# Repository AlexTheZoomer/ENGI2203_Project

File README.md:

# 🏛️ Integrated Security System for Museum & Showcase Environments 

## Project Overview
This project is an **Integrated Security System** designed for museum and showcase environments, providing security through **object tagging, proximity detection, and real-time monitoring**. The following repository will be holding the software project components (C Files & Solidworks Models). Future iterations may include automated alerts. The system aims to mitigate **theft, unauthorized access, and display damage**, while also offering valuable data for monitoring and management.

## Features
- **RFID-Based Pedestal Monitoring**
- **Tiered Alert System** with LED Indicators & Alarms
- **Automated Security Responses** (Door Closures, Logs, Alarms)
- **Low-Cost Implementation** using **Arduino Nano Compatible Boards**
- **Integration with Museum Databases** for authentication

## Functional Requirements
### 1. Pedestal Authorization System
- A **photoresistor** detects object presence.
- The object **communicates via RFID** with the pedestal.
- If the RFID tag matches the database, a **green LED** confirms correct placement.
- If removed or mismatched, **warning and alarm sequences** initiate.

### 2. Security Events
Each event corresponds with a different LED and response:
| Event | LED Color | Response |
|---|---|---|
| Correct Placement | Green | Normal Operation |
| Missing Item | Orange | Slow Beep & Warning |
| Incorrect Item | Blue | Long Alarm Beep |
| Unauthorized Item | Red | Fast Alarm, Door Lock |

### 3. Automated Door System
- Remains open with correct placement.
- Closes after item removal if **security escalation** occurs.

## Hardware Components
- **Microcontroller:** ATMega328p (Arduino Nano compatible)
- **RFID Receiver & Transmitter Modules**
- **Photoresistors for Object Detection**
- **LED Indicators** (Green, Orange, Blue, Red)
- **Alarm Speaker**
- **Servo Motor for Door Automation**

## Software Components
- **Embedded C Code** to manage:
  - Authentication
  - Security Protocols
  - Logging System Events
- **Logging & Audit Trail** for museum security personnel

## Installation & Setup
1. Mount **pedestal module** and connect power.
2. Attach RFID tags to **displayed artifacts**.
3. Load **museum database IDs** onto the system.
4. Configure security thresholds and responses.

## Team Members & Roles
- **Alexandre DesAulniers** - Communications Lead & GitHub Management
- **Mason Allain** - Hardware Design Lead
- **Michael Gallant** - Software Design Lead
- **Sadie Fowlow** - Team Member

## Project Timeline
| Milestone | Date |
|---|---|
| Conceptual Design & Planning | February 12, 2025 |
| Hardware Prototyping Begins | March 1, 2025 |
| Functional Prototype Completed | March 17, 2025 |
| Final Testing & Report | April 7, 2025 |

## Future Work
- **Enhance RFID Security Measures** (Encryption & Anti-Tamper Features)
- **Improve False Alarm Mitigation**
- **Develop Remote Monitoring Dashboard**
- **Expand Compatibility with Existing Museum Security Systems**

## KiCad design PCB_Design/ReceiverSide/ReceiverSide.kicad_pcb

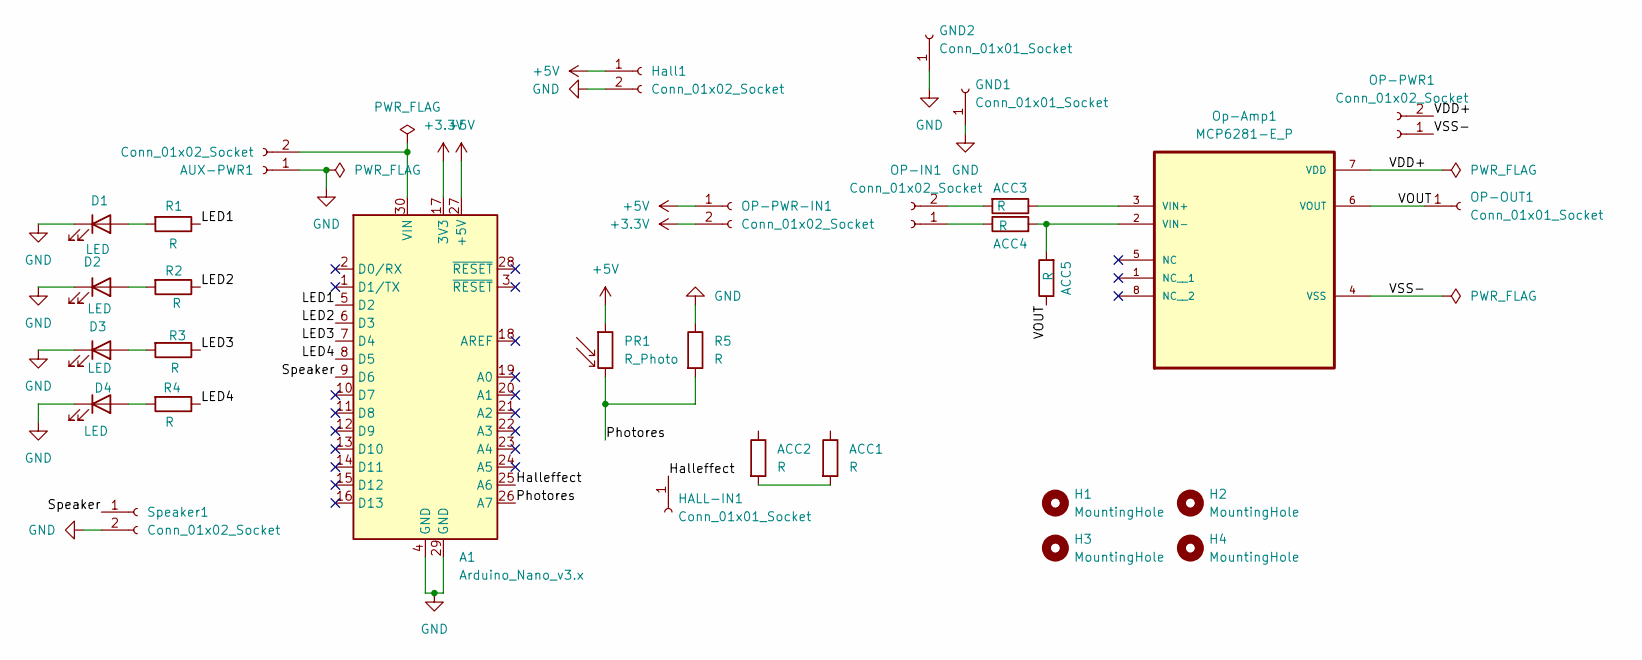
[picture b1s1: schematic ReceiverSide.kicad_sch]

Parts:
A1: Arduino_Nano_v3.x; Arduino_Nano
ACC1, ACC2, ACC3, ACC4, ACC5: R; R_Axial_DIN0204_L3.6mm_D1.6mm_P5.08mm_Horizontal
AUX-PWR1: Conn_01x02_Socket; PinSocket_1x02_P2.54mm_Vertical
D1, D2, D3, D4: LED; LED_D3.0mm
GND1, GND2: Conn_01x01_Socket; PinSocket_1x01_P2.54mm_Vertical
H1, H2, H3, H4: MountingHole; MountingHole_2.7mm
HALL-IN1: Conn_01x01_Socket; PinSocket_1x01_P2.54mm_Vertical
Hall1: Conn_01x02_Socket; PinSocket_1x02_P2.54mm_Vertical
OP-IN1: Conn_01x02_Socket; PinSocket_1x02_P2.54mm_Vertical
OP-OUT1: Conn_01x01_Socket; PinSocket_1x01_P2.54mm_Vertical
OP-PWR1: Conn_01x02_Socket; PinSocket_1x02_P2.54mm_Vertical
OP-PWR-IN1: Conn_01x02_Socket; PinSocket_1x02_P2.54mm_Vertical
Op-Amp1: MCP6281-E_P; DIP787W46P254L927H533Q8
PR1: R_Photo; R_Axial_DIN0204_L3.6mm_D1.6mm_P5.08mm_Horizontal
R1, R2, R3, R4, R5: R; R_Axial_DIN0204_L3.6mm_D1.6mm_P5.08mm_Horizontal
Speaker1: Conn_01x02_Socket; PinSocket_1x02_P2.54mm_Vertical

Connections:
+3.3V: A1.17 (3V3), OP-PWR-IN1.2
+5V: A1.27 (+5V), Hall1.1, OP-PWR-IN1.1, PR1.1
/Halleffect: A1.25 (A6), HALL-IN1.1
/LED1: A1.5 (D2), R1.1
/LED2: A1.6 (D3), R2.1
/LED3: A1.7 (D4), R3.1
/LED4: A1.8 (D5), R4.1
/Photores: A1.26 (A7), PR1.2, R5.2
/Speaker: A1.9 (D6), Speaker1.1
/VDD+: OP-PWR1.2, Op-Amp1.7 (VDD)
/VOUT: ACC5.1, OP-OUT1.1, Op-Amp1.6 (VOUT)
/VSS-: OP-PWR1.1, Op-Amp1.4 (VSS)
GND: A1.4 (GND), A1.29 (GND), AUX-PWR1.1, D1.1 (K), D2.1 (K), D3.1 (K), D4.1 (K), GND1.1, GND2.1, Hall1.2, R5.1, Speaker1.2
unnamed: A1.30 (VIN), AUX-PWR1.2
unnamed: ACC1.2, ACC2.2
unnamed: D1.2 (A), R1.2
unnamed: D2.2 (A), R2.2
unnamed: D3.2 (A), R3.2
unnamed: D4.2 (A), R4.2
unnamed: ACC4.1, OP-IN1.1
unnamed: ACC3.2, OP-IN1.2
unnamed: ACC3.1, Op-Amp1.3 (VIN+)
unnamed: ACC4.2, ACC5.2, Op-Amp1.2 (VIN-)

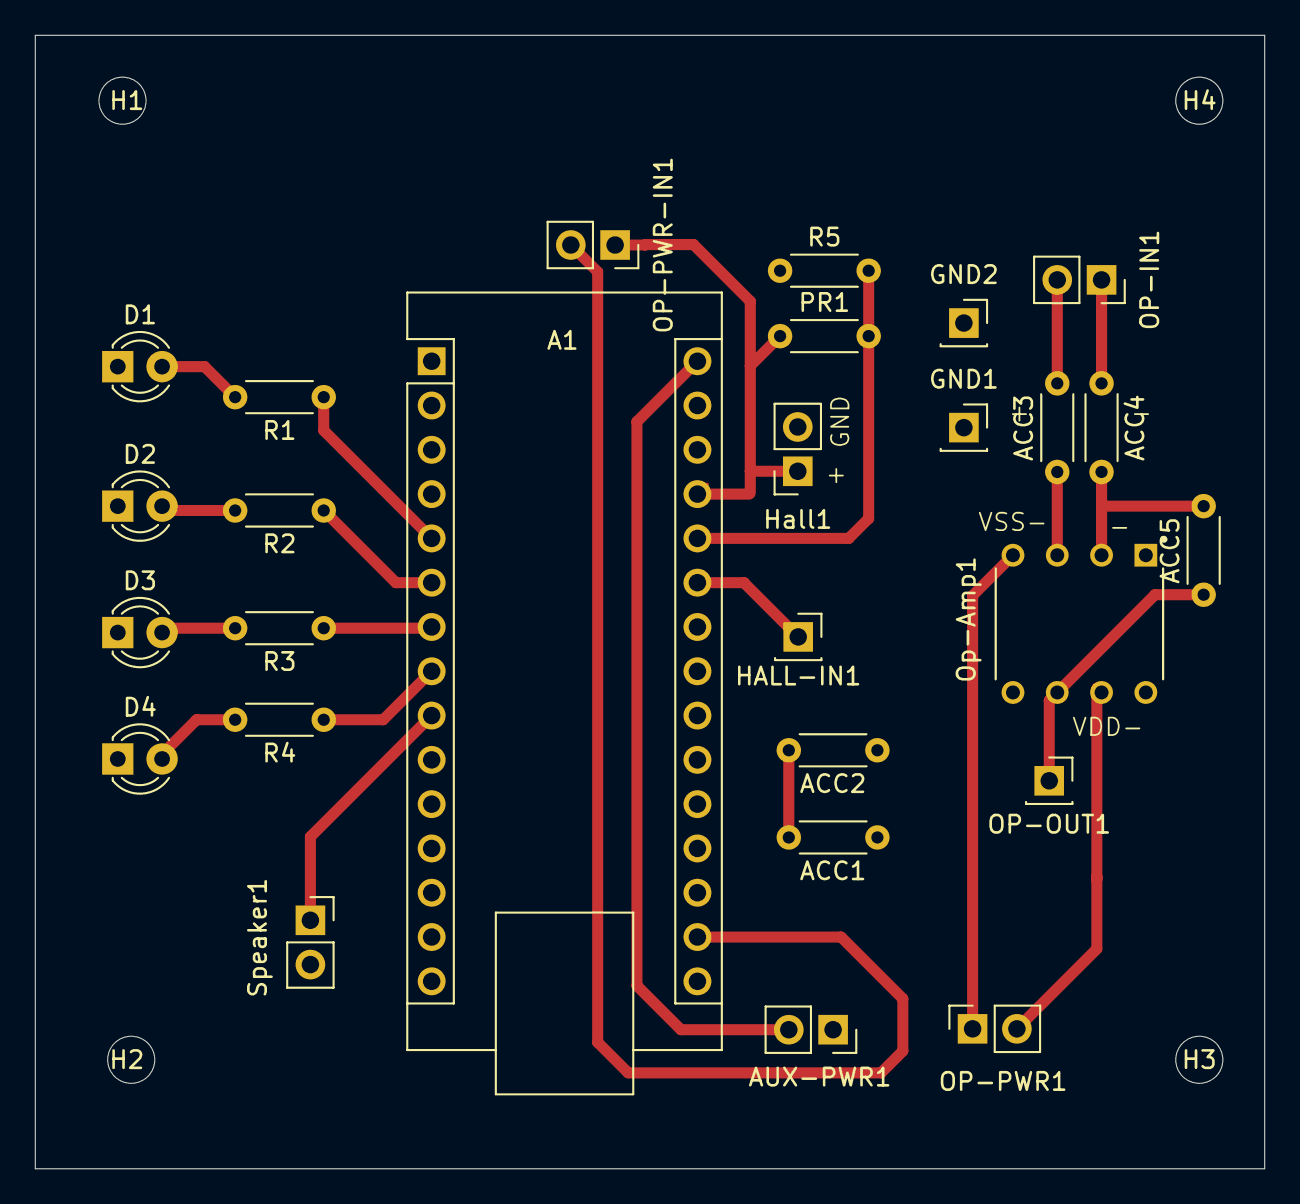
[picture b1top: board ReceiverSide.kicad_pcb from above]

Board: 2 copper layers, 70.5 x 65.0 mm, 31 parts (0 on the bottom side), 23 nets.

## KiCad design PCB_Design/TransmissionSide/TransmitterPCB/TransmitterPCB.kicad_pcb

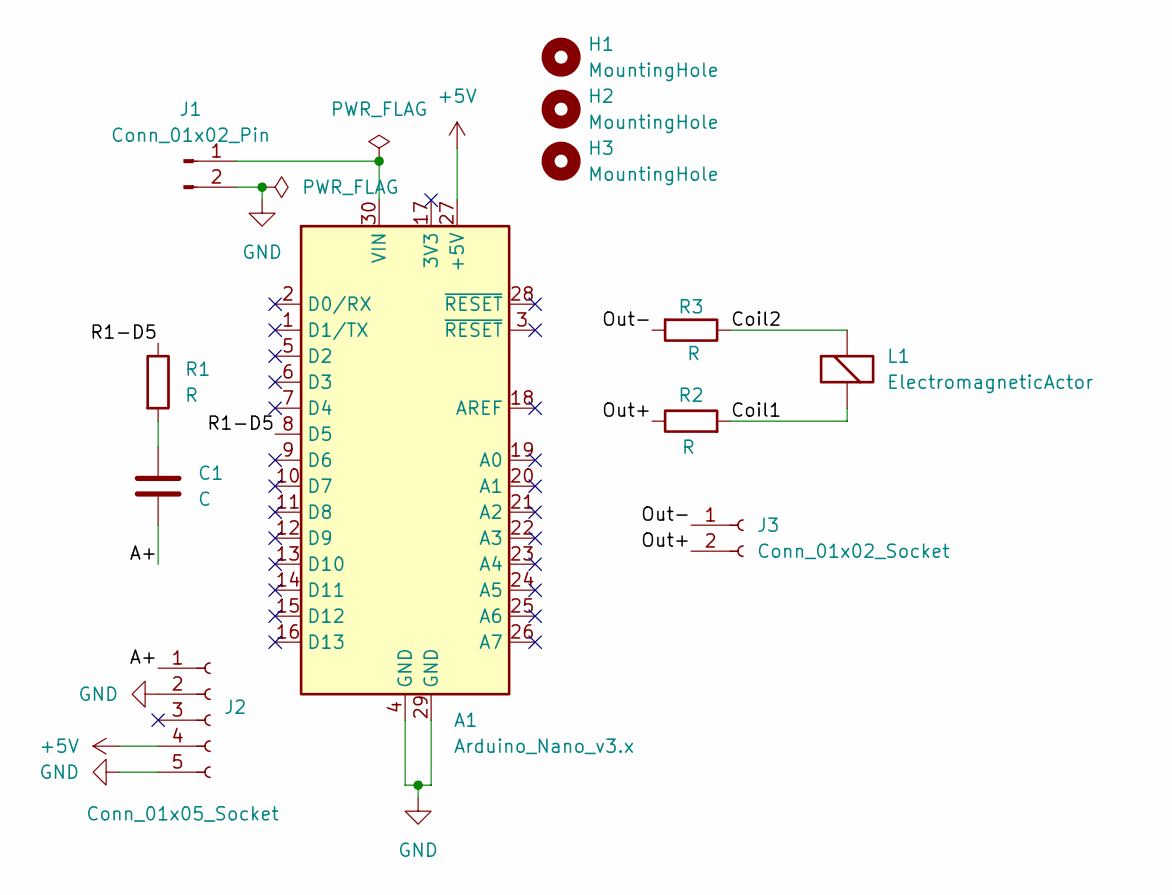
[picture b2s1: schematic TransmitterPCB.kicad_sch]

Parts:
A1: Arduino_Nano_v3.x; Arduino_Nano
C1: C; R_Axial_DIN0204_L3.6mm_D1.6mm_P5.08mm_Horizontal
H1, H2, H3: MountingHole; MountingHole_2.7mm
J1: Conn_01x02_Pin; PinSocket_1x02_P2.54mm_Vertical
J2: Conn_01x05_Socket; PinSocket_1x05_P2.54mm_Vertical
J3: Conn_01x02_Socket; R_Axial_DIN0204_L3.6mm_D1.6mm_P5.08mm_Horizontal
L1: ElectromagneticActor; R_Axial_DIN0204_L3.6mm_D1.6mm_P5.08mm_Horizontal
R1: R; R_Axial_DIN0204_L3.6mm_D1.6mm_P5.08mm_Horizontal
R2, R3: R; R_Axial_DIN0207_L6.3mm_D2.5mm_P7.62mm_Horizontal

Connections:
+5V: A1.27 (+5V), J2.4
/A+: C1.2, J2.1
/Coil1: L1.2 (+), R2.2
/Coil2: L1.1 (-), R3.1
/Out+: J3.2, R2.1
/Out-: J3.1, R3.2
/R1-D5: A1.8 (D5), R1.1
GND: A1.4 (GND), A1.29 (GND), J1.2, J2.2, J2.5
unnamed: A1.30 (VIN), J1.1
unnamed: C1.1, R1.2

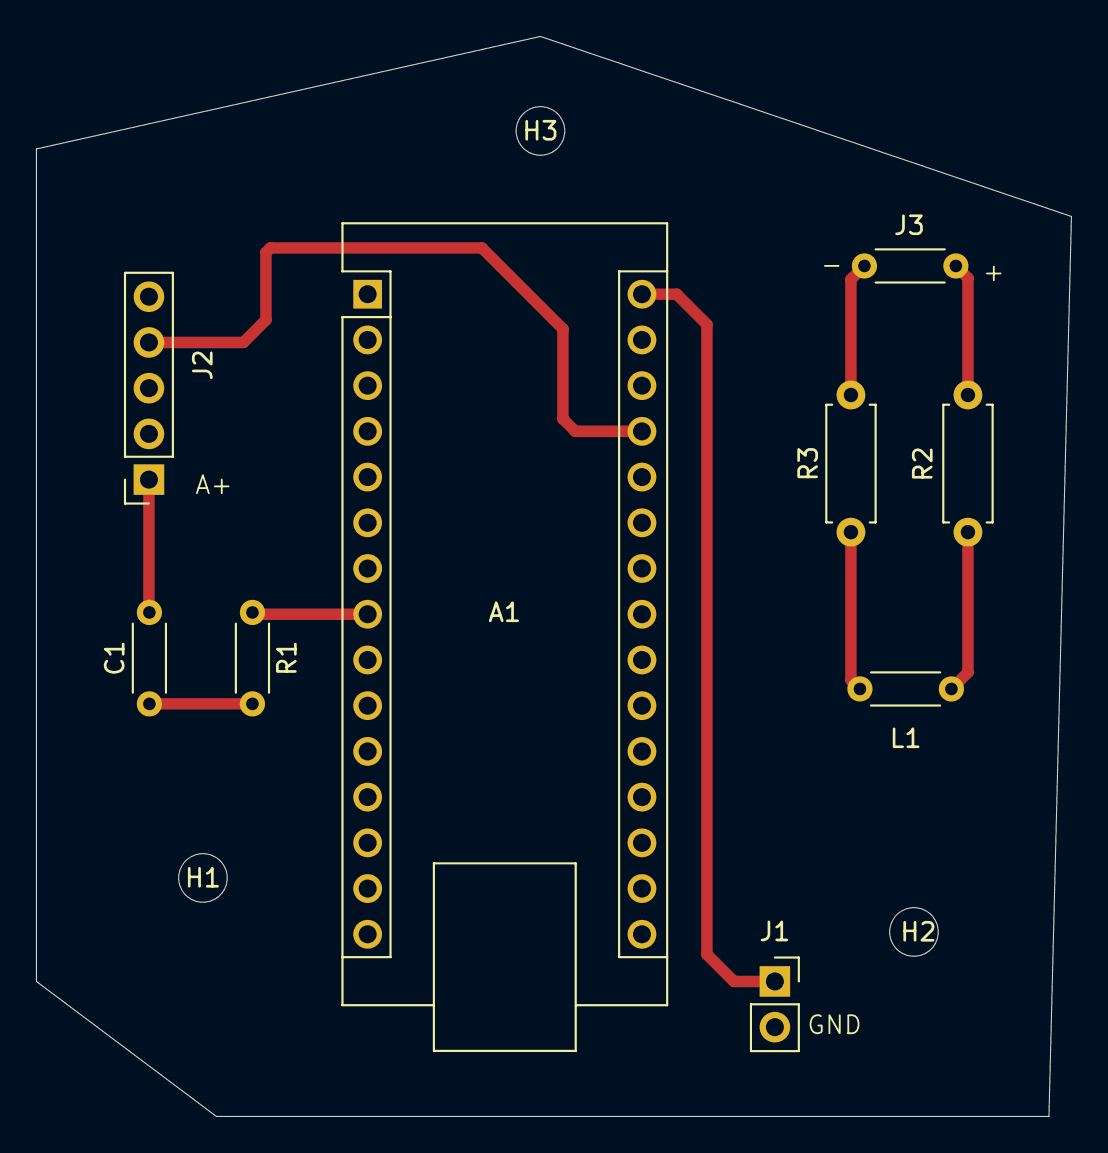
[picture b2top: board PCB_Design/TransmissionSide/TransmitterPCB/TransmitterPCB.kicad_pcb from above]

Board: 2 copper layers, 57.5 x 60.0 mm, 12 parts (0 on the bottom side), 10 nets.

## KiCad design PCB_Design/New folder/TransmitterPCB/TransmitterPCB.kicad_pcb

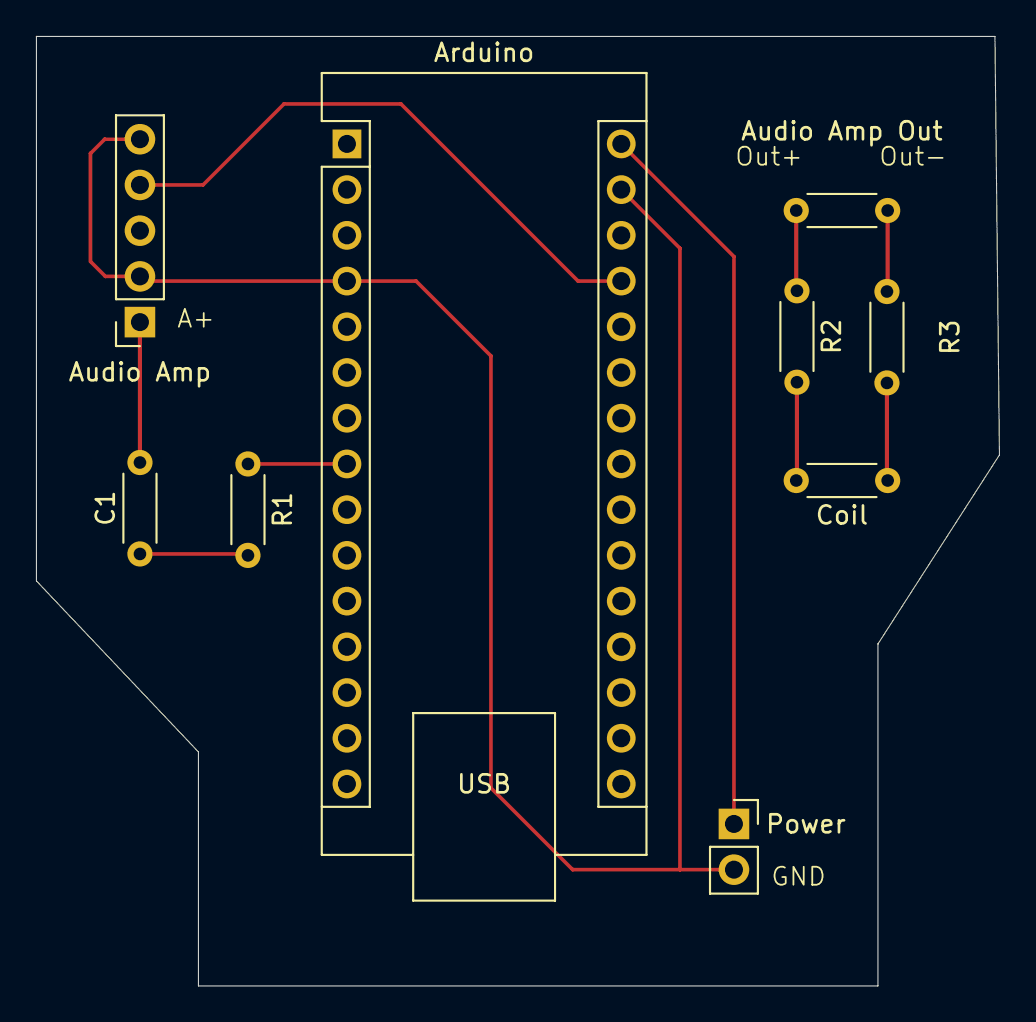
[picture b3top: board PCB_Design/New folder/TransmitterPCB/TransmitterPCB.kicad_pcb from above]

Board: 2 copper layers, 53.5 x 52.8 mm, 9 parts (0 on the bottom side), 10 nets.

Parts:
Arduino: Arduino_Nano_v3.x; Arduino_Nano
Audio Amp: Conn_01x05_Socket; PinSocket_1x05_P2.54mm_Vertical
Audio Amp Out: Conn_01x02_Socket; R_Axial_DIN0204_L3.6mm_D1.6mm_P5.08mm_Horizontal
C1: C; R_Axial_DIN0204_L3.6mm_D1.6mm_P5.08mm_Horizontal
Coil: ElectromagneticActor; R_Axial_DIN0204_L3.6mm_D1.6mm_P5.08mm_Horizontal
Power: Conn_01x02_Pin; PinSocket_1x02_P2.54mm_Vertical
R1, R2, R3: R; R_Axial_DIN0204_L3.6mm_D1.6mm_P5.08mm_Horizontal

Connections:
+5V: Arduino.27 (+5V), Audio Amp.4
/A+: Audio Amp.1, C1.2
/Coil1: Coil.2 (+), R2.2
/Coil2: Coil.1 (-), R3.1
/Out+: Audio Amp Out.2, R2.1
/Out-: Audio Amp Out.1, R3.2
/R1-D5: Arduino.8 (D5), R1.1
GND: Arduino.4 (GND), Arduino.29 (GND), Audio Amp.2, Audio Amp.5, Power.2
unnamed: Arduino.30 (VIN), Power.1
unnamed: C1.1, R1.2

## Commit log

2025-02-18 tesr
2025-02-18 wipe
2025-02-18 test
2025-02-18 pedestal base
2025-02-21 Created README.md
2025-02-22 module 1 sample for report
2025-02-22 Added Bowl Model
2025-02-28 document folder and team contract uploaded
2025-03-09 Added initial transmission code, working on Sine wave
2025-03-09 PCB folder and KiCad file
2025-03-10 rev2 - receiver code - mason
2025-03-10 Components added to schematic
2025-03-10 70Hz Sine Inverter finished, looking to up frequency to improve data rate
2025-03-10 Schematic connected and placed in pcb editor
2025-03-10 Revert "Update .atsuo"
    This reverts commit 41066e8acf1d2cf720b2caad11047eecd35b3621.
2025-03-10 Git clean up and addition of MCS file for receiver
2025-03-10 Updated Clock cycle, 800hz reached. Added Second Top Register for 200hz-300hz modulation
2025-03-11 Transmitter PCB temp layout
2025-03-11 some edits on receiver side
2025-03-11 Transmitter PCB finished... maybe
2025-03-11 transmitter pcb
2025-03-11 xxxx
2025-03-11 fix2
2025-03-11 fugh
2025-03-11 fix4
2025-03-11 fix5
2025-03-11 okay we are fixed.... i think
2025-03-11 FIXED
2025-03-12 update fixed
2025-03-12 COMPLETED TRANSMITTER PCB - YAYYYYYYY
2025-03-12 COMPLETED RECIVER PCB
2025-03-12 PCB DONE
2025-03-18 Updated CAD'
2025-03-20 CAD Finished
2025-03-20 Export files
2025-03-23 Updated Transmission Code, now can transmit a 16 bit string
2025-03-25 updated receiver code 03/25
2025-03-28 new receive
2025-04-07 Final transmission code
